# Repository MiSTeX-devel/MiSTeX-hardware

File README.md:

# MiSTeX-hardware

## Current
### MiSTeX baseboard for QMTech form factor FPGA boards
The 
baseboard is the current recommended platform. It can be used with Raspberry Pi Zero
form factor SBCs and QMTech form factor core boards.
Status: The `rev2` revision has been manufactured and tested working.

### Using the Raspberry Pi Zero with MiSTeX, with a generic FPGA board
To connect the Raspberry Pi Zero to the FPGA board of your choice,
the pin mappings can be found in two places:
1. On the FPGA board side the pin mappings are defined in the board support file in MiSTeX-boards:
   
2. On the Raspberry Pi Zero side, the pin mappings of the GPIO control signals are defined in Main_MiSTeX in fpga_io.cpp:

   And the SPI bus is the SPI0 on the Raspberry Pi header:

## Obsolete
### MiSTeX Pmod
Status: Manufactured, waiting for arrival. Obsolete, Sipeed Lich

### MiSTeX cape for the Terasic DECA board
Status: Manufactured and tested working.

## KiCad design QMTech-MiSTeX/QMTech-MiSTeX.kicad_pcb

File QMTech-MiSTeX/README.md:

# **MiSTeX Board**

### Connectors and main headers

- Headers for QMTech 128 pins FPGA format (2x 2x32)
- MiSTer SDRAM module header (Terasic 2x20)
- RPi header (Orange Pi 2W) (2x20)
- SNAC user port for gamepads / mt32pi (USB3)
- VGA video out (DB15)
- HDMI video out
- Analog audio out (delta sigma) (jack 3.5) 
- SPDID audio out (Toslink)
- Secondary uSD Card
- PMOD J11 header (GPIO / I2S / Delta-sigma)
- USB C for RP2040 programming
- USB C power supply

### Power Supply

It is recommended to use the USB power port since it uses a voltage filter. This port supply power to FPGA and Orange Pi as well.

The Jumper on the power port is for an external power switch mounted in a case for example. 

<u>J18 needs to be shorted with a jumper if no switch is placed</u>.

You can of course also power the board from the core board barrel jack.

### FPGA programming

Connect an USB-C from RP2040 port to the USB HUB you are using

Connect Dupont wires from FPGA JTAG to JTAG header on MiSTeX board

### Switches / Jumpers / small headers / Leds

J9 RC2040 Boot jumper. Short to reprogram RC2040 firmware

J10 SCART VGA pin 9 jumper. Short to use a VGA to SCART cable

J18 Power switch (or either place a jumper if no switch is added)

IO6 Jumper - By default shorted 2-3 for most gamepads. Some accessories require additional 3V3 power supply, in that case put jumper in position 1-2 next to +3V3 text.

SW1 Button User (RPi/Orange Pi)

SW2 Button OSD  (RPi/Orange Pi)

SW3 Button Reset  (RPi/Orange Pi)

SW4 Button Menu  (RPi/Orange Pi)

The side switches SW5, SW6 are currently unused and have been erroneously momentary in rev1, but should actually be latching which has been fixed in rev2

- SW5 (FPGA) will be used to switch the Pmod signals from I2S to general purpose use

- SW6 (RPi/Orange Pi)  is intended to switch the SNAC port from SNAC to mt32pi mode

The DIP switches are currently unused too  (RPi/Orange Pi).

User / HDD / Power Leds

DBG J7 Debug UART (RC2040)

SWD J12 Header (RC2040)

JTAG J6 Header   (RC2040)

ADC J14 Header (3 ADC + 1 GPIO)  (RC2040)

### SD image (placed at Orange Pi SD slot)

```sh
$ wget -c http://www.hans-baier.de/static/mistex-orangepizero2w.img.xz
$ md5sum mistex-orangepizero2w.img.xz
30ea6324ea5340d76d8ffbd25d986887  mistex-orangepizero2w.img.xz
```

The boot image needs the menu core at /media/fat/menu.bit
or menu.rbf for Altera boards
The sdcard image above is preconfigured for the Artix 100t QmTech with pre built cores
But A200T and K325T cores are included too
You only need to copy the right one to menu.bit

### RP2040 firmware

You need to bridge the boot jumper J9 and plug the RC2040 USB port into a PC to flash this firmware: https://github.com/MiSTeX-devel/pico-dirtyJtag/releases/tag/v0.0.1
The core FPGA board needs to be present there because it powers the 2040 except you power the 3.3v rails from another source.

Connect power supply either to FPGA barrel or USB-C power port.

Copy the uf2 file into the mass storage device that appears on PC. When the file disappears it means it is flashing the firmware. Wait a bit and disconnect USB-C and remove jumper.

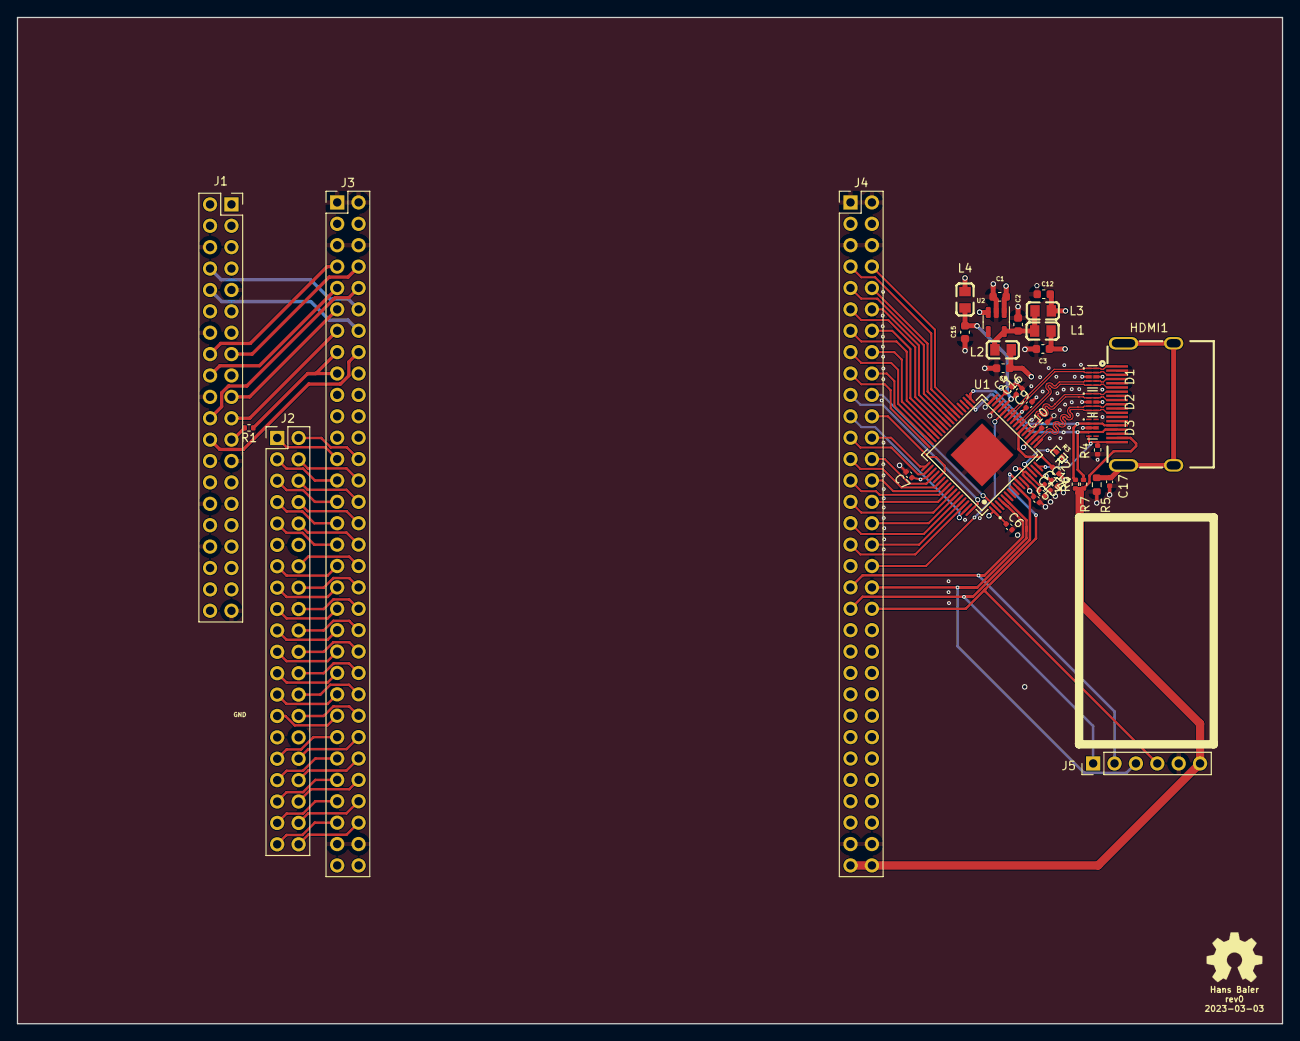
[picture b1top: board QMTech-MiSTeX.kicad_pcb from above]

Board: 4 copper layers, 150.2 x 119.5 mm, 40 parts (0 on the bottom side), 104 nets.

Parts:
C1: 1u; C_0603_1608Metric
C2, C3, C8, C12, C15: 10u; C_0603_1608Metric
C4, C5, C6, C7, C9, C10, C11, C13, C14, C16, C17: 100nF; C_0402_1005Metric
D1, D2, D3: TPD4E05U06DQAR_C2972498; DFN2510-10_L2.5-W1.0-P0.50-BL
HDMI1: HDMI-001S; HDMI-SMD_HDMI-001S
J1: RPi_GPIO; PinSocket_2x20_P2.54mm_Vertical
J2: MiSTer SDRAM Module; PinHeader_2x20_P2.54mm_Vertical
J3, J4: Conn_02x32_Odd_Even; PinHeader_2x32_P2.54mm_Vertical
J5: Conn_01x06_Male; PinHeader_1x06_P2.54mm_Vertical
L1, L2, L3, L4: 10uH; L0805
N1: OHWLOGO; OSHW-Symbol_6.7x6mm_SilkScreen
R1: 51R; R_0402_1005Metric
R2, R6, R7: 2k; R_0402_1005Metric
R3: 887R; R0402
R4: 10k; R_0402_1005Metric
R5: 1M; R_0603_1608Metric
U1: ADV7513BSWZ; LQFP-64_L10.0-W10.0-P0.50-LS12.0-BL-EP5.3
U2: TPS76318; SOT-23-5

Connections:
+1V8: C2.1, L1.1, L2.1, L3.1, U2.5 (VOUT)
+3V3: C1.1, J2.29, J3.3, J3.4, J4.3, J4.4, L4.1, U2.1 (VIN), U2.3 (EN)
+5V: HDMI1.18 (+5VPower), J1.2 (5V), J1.4 (5V), J2.11, J3.63, J3.64, J4.63, J4.64, J5.6, R6.1, R7.2
/1V8_AVDD: C8.1, C9.1, C10.1, C11.1, L2.2, U1.15 (AVDD), U1.19 (AVDD), U1.25 (AVDD)
/1V8_DVDD: C3.1, C4.1, C5.1, C6.1, C7.1, L1.2, U1.1 (DVDD), U1.11 (DVDD), U1.31 (DVDD), U1.51 (DVDD)
/1V8_PVDD: C12.1, C13.1, C14.1, L3.2, U1.12 (PVDD), U1.13 (BGVDD)
/3V3_DVDD: C15.1, C16.1, L4.2, U1.29 (DVDD_3V)
/DDC_SCL: D3.2 (D1-), D3.9 (NC), HDMI1.15 (SCL), R6.2, U1.33 (DDCSCL)
/DDC_SDA: D3.4 (D2+), D3.7 (NC), HDMI1.16 (SDA), R7.1, U1.34 (DDCSDA)
/FPGA_EN: J1.16 (GPIO23), J3.7
/FPGA_RESET: J1.15 (GPIO22), J3.8
/HDMI_CLK+: D2.4 (D2+), D2.7 (NC), HDMI1.10 (TMDSClock+), U1.18 (TXC+)
/HDMI_CLK-: D2.5 (D2-), D2.6 (NC), HDMI1.12 (TMDSClock-), U1.17 (TXC–)
/HDMI_HPD: D3.5 (D2-), HDMI1.19 (HotPlugDetect), R4.1, U1.16 (HPD)
/HDMI_TX0+: D2.1 (D1+), D2.10 (NC), HDMI1.7 (TMDSData0+), U1.21 (TX0+)
/HDMI_TX0-: D2.2 (D1-), D2.9 (NC), HDMI1.9 (TMDSData0-), U1.20 (TX0–)
/HDMI_TX1+: D1.4 (D2+), D1.7 (NC), HDMI1.4 (TMDSData1+), U1.24 (TX1+)
/HDMI_TX1-: D1.5 (D2-), D1.6 (NC), HDMI1.6 (TMDSData1-), U1.23 (TX1–)
/HDMI_TX2+: D1.1 (D1+), D1.10 (NC), HDMI1.1 (TMDSData2+), U1.27 (TX2+)
/HDMI_TX2-: D1.2 (D1-), D1.9 (NC), HDMI1.3 (TMDSData2-), U1.26 (TX2–)
/I2C_SCL: J1.5 (GPIO03_SCL1_I2C), U1.35 (SCL)
/I2C_SDA: J1.3 (GPIO02_SDA1_I2C), U1.36 (SDA)
/I2S_DAT: J4.38, J5.3, U1.5 (I2S0)
/I2S_LRCLK: J4.40, J5.4, U1.10 (LRCLK)
/I2S_MCLK: J4.37, J5.2, U1.4 (MCLK)
/I2S_SCLK: J4.39, J5.1, U1.9 (SCLK)
/IO_EN: J1.22 (GPIO25), J3.10
/OSD_EN: J1.18 (GPIO24), J3.9
/RAM_A0: J2.37, J3.57
/RAM_A1: J2.38, J3.58
/RAM_A2: J2.39, J3.59
/RAM_A3: J2.40, J3.60
/RAM_A4: J2.28, J3.50
/RAM_A5: J2.25, J3.47
/RAM_A6: J2.26, J3.48
/RAM_A7: J2.23, J3.45
/RAM_A8: J2.24, J3.46
/RAM_A9: J2.21, J3.43
/RAM_A10: J2.36, J3.56
/RAM_A11: J2.22, J3.44
/RAM_A12: J2.19, J3.41
/RAM_BA0: J2.34, J3.54
/RAM_BA1: J2.35, J3.55
/RAM_CAS: J2.31, J3.51
/RAM_CLK: J2.20, J3.42
/RAM_CS: J2.33, J3.53
/RAM_DQ0: J2.1, J3.25
/RAM_DQ1: J2.2, J3.26
/RAM_DQ2: J2.3, J3.27
/RAM_DQ3: J2.4, J3.28
/RAM_DQ4: J2.5, J3.29
/RAM_DQ5: J2.6, J3.30
/RAM_DQ6: J2.7, J3.31
/RAM_DQ7: J2.8, J3.32
/RAM_DQ8: J2.18, J3.40
/RAM_DQ9: J2.17, J3.39
/RAM_DQ10: J2.16, J3.38
/RAM_DQ11: J2.15, J3.37
/RAM_DQ12: J2.14, J3.36
/RAM_DQ13: J2.13, J3.35
/RAM_DQ14: J2.10, J3.34
/RAM_DQ15: J2.9, J3.33
/RAM_RAS: J2.32, J3.52
/RAM_WE: J2.27, J3.49
/RGB_CLK: J4.22, U1.53 (CLK)
/RGB_D0: J4.33, U1.62 (D0)
/RGB_D1: J4.34, U1.61 (D1)
/RGB_D2: J4.31, U1.60 (D2)
/RGB_D3: J4.32, U1.59 (D3)
/RGB_D4: J4.29, U1.58 (D4)
/RGB_D5: J4.30, U1.57 (D5)
/RGB_D6: J4.27, U1.56 (D6)
/RGB_D7: J4.28, U1.55 (D7)
/RGB_D8: J4.25, U1.54 (D8)
/RGB_D9: J4.26, U1.52 (D9)
/RGB_D10: J4.23, U1.50 (D10)
/RGB_D11: J4.24, U1.49 (D11)
/RGB_D12: J4.17, U1.48 (D12)
/RGB_D13: J4.18, U1.47 (D13)
/RGB_D14: J4.15, U1.46 (D14)
/RGB_D15: J4.16, U1.45 (D15)
/RGB_D16: J4.13, U1.44 (D16)
/RGB_D17: J4.14, U1.43 (D17)
/RGB_D18: J4.11, U1.42 (D18)
/RGB_D19: J4.12, U1.41 (D19)
/RGB_D20: J4.9, U1.40 (D20)
/RGB_D21: J4.10, U1.39 (D21)
/RGB_D22: J4.7, U1.38 (D22)
/RGB_D23: J4.8, U1.37 (D23)
/RGB_DE: J4.21, U1.63 (DE)
/RGB_HSYNC: J4.19, U1.64 (HSYNC)
/RGB_INT: J4.36, U1.28 (INT)
/RGB_VSYNC: J4.20, U1.2 (VSYNC)
/SPI_CLK: J3.15, J3.17, R1.1
/SPI_CS: J1.24 (GPIO08_SPI_CE0_N), J3.16
/SPI_MISO: J1.21 (GPIO09_SPI_MISO), J3.13
/SPI_MOSI: J1.19 (GPIO10_SPI_MOSI), J3.11
/UART_RX: J1.10 (GPIO15_RXD0), J3.14
/UART_TX: J1.8 (GPIO14_TXD0), J3.12
GND: C1.2, C2.2, C3.2, C4.2, C5.2, C6.2, C7.2, C8.2, C9.2, C10.2, C11.2, C12.2, C13.2, C14.2, C15.2, C16.2, C17.2, D1.3 (GND), D1.8 (GND), D2.3 (GND), D2.8 (GND), D3.3 (GND), D3.8 (GND), HDMI1.2 (TMDSData2Shield), HDMI1.5 (TMDSData1Shield), HDMI1.8 (TMDSData0Shield), HDMI1.11 (TMDSClockShield), HDMI1.17 (DDC/CECGround), J1.6 (GND), J1.9 (GND), J1.14 (GND), J1.20 (GND), J1.25 (GND), J1.30 (GND), J1.34 (GND), J1.39 (GND), J2.12, J2.30, J3.1, J3.2, J3.5, J3.6, J3.61, J3.62, J4.1, J4.2, J4.5, J4.6, J4.61, J4.62, J5.5, R2.2, R3.1, R4.2, R5.2, U1.30 (CEC), U1.32 (CEC_CLK), U1.65 (EP), U2.2 (GND)
unnamed: C17.1, HDMI1.20 (GND), HDMI1.21 (GND), HDMI1.22 (GND), HDMI1.23 (GND), R5.1
unnamed: J1.23 (GPIO11_SPI_CLK), R1.2
unnamed: R2.1, U1.22 (PD)
unnamed: R3.2, U1.14 (R_EXT)

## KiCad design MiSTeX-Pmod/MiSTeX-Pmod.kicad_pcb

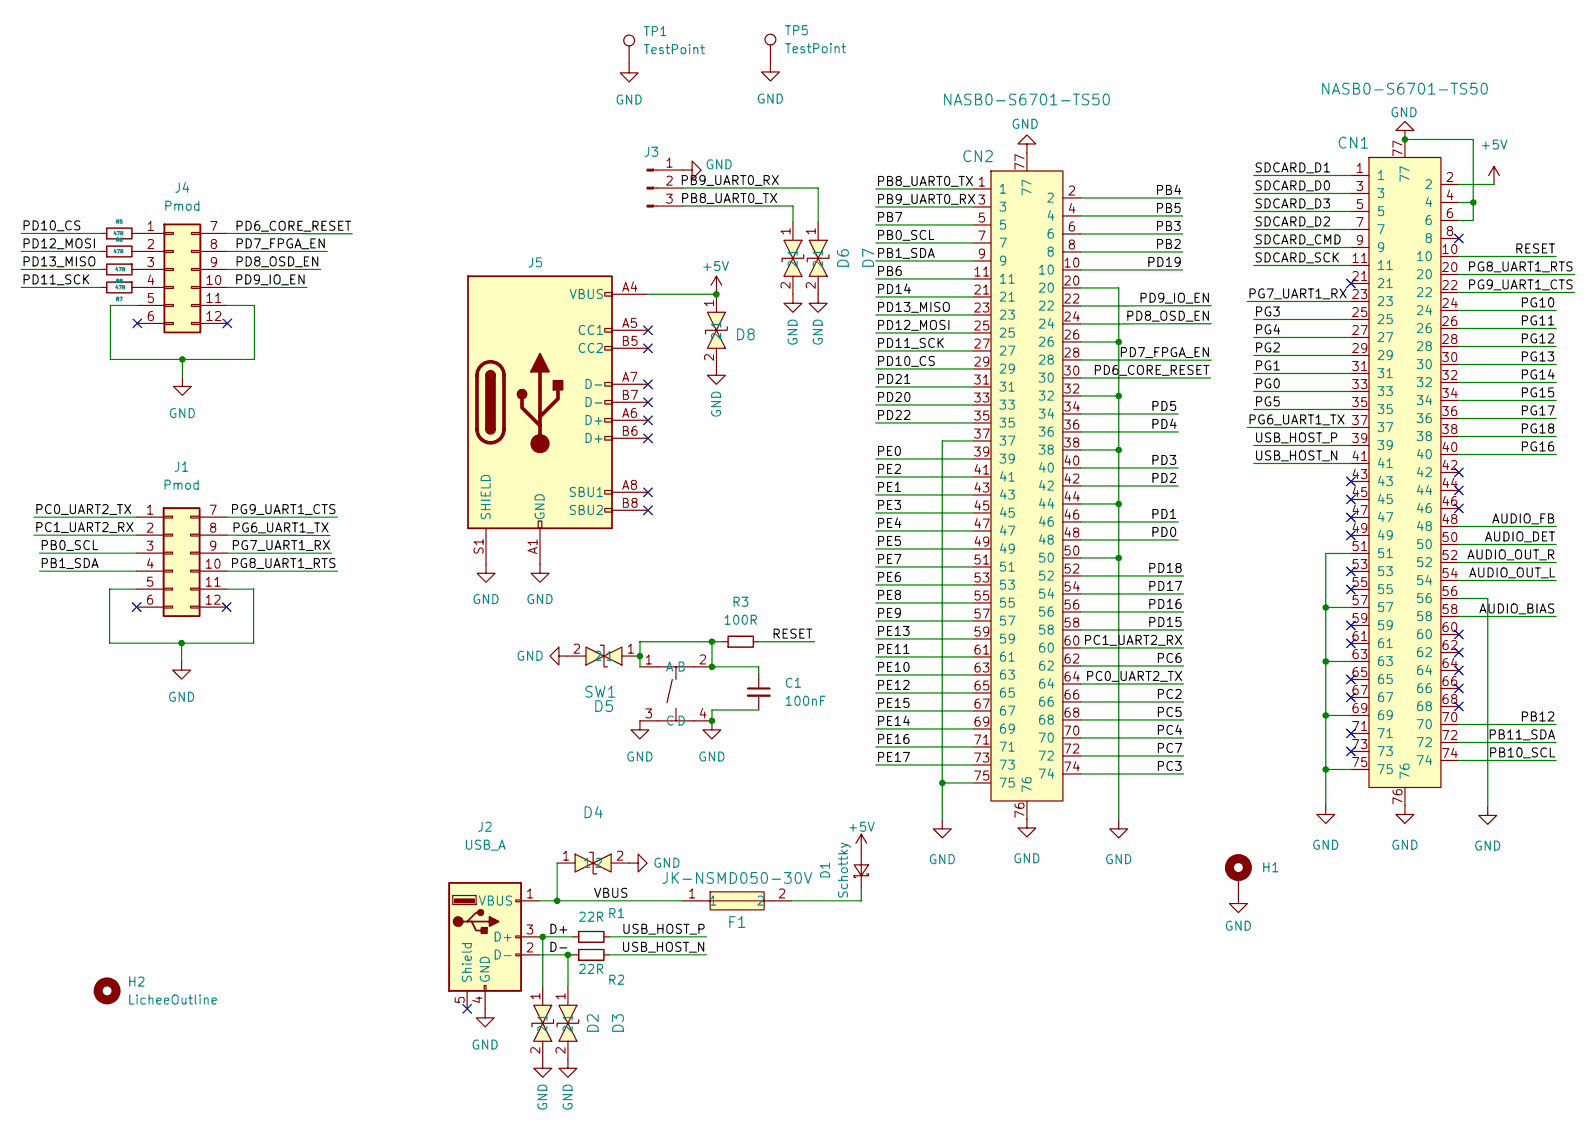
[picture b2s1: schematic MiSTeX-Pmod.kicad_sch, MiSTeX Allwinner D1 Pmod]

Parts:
C1: 100nF; C_0402_1005Metric; LCSC C1525
CN1, CN2: NASB0-S6701-TS50; CONN-SMD_67P-P0.50-V_NASB0-S6701-TS50; LCSC Part C367024
D1: Schottky; D_SMA; LCSC C22452
D2, D3, D4, D5, D6, D7, D8: LXES15AAA1-133; D0402-BI; LCSC Part C191267
F1: JK-NSMD050-30V; F1206; LCSC Part C720075
H1: MountingHole_Pad; MountingHole_2.2mm_M2_ISO7380_Pad_TopBottom
H2: LicheeOutline
J1, J4: Pmod; Pmod 2x6
J2: USB_A; USB-A-SMD_GT-USB-2004-CWG1A; LCSC C5117890
J3: Conn_01x03_Male; PinHeader_1x03_P2.54mm_Vertical
J5: Connector_USB_C_Receptacle_USB2.0; USB-C_SMD-TYPE-C-31-M-12; LCSC C165948
R1, R2: 22R; R_0402_1005Metric; LCSC C25092
R3: 100R; R_0402_1005Metric; LCSC C25076
R5, R6, R7, R8: 47R; R_0402_1005Metric; LCSC C25118
SW1: TS-1187A-B-A-B; SW-SMD_4P-L5.1-W5.1-P3.70-LS6.5-TL-2; LCSC Part C318884
TP1: TestPoint; TestPoint_Pad_D2.0mm
TP5: TestPoint; TestPoint_Pad_D1.0mm

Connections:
+5V: CN1.2, D1.2 (A), D8.1, J5.A4 (VBUS), J5.A9 (VBUS), J5.B4 (VBUS), J5.B9 (VBUS)
/AUDIO_BIAS: CN1.58
/AUDIO_DET: CN1.50
/AUDIO_FB: CN1.48
/AUDIO_OUT_L: CN1.54
/AUDIO_OUT_R: CN1.52
/D+: D2.1, J2.3 (D+), R1.1
/D-: D3.1, J2.2 (D-), R2.1
/PB0_SCL: CN2.7, J1.3
/PB1_SDA: CN2.9, J1.4
/PB2: CN2.8
/PB3: CN2.6
/PB4: CN2.2
/PB5: CN2.4
/PB6: CN2.11
/PB7: CN2.5
/PB8_UART0_TX: CN2.1, D6.1, J3.3
/PB9_UART0_RX: CN2.3, D7.1, J3.2
/PB10_SCL: CN1.74
/PB11_SDA: CN1.72
/PB12: CN1.70
/PC0_UART2_TX: CN2.64, J1.1
/PC1_UART2_RX: CN2.60, J1.2
/PC2: CN2.66
/PC3: CN2.74
/PC4: CN2.70
/PC5: CN2.68
/PC6: CN2.62
/PC7: CN2.72
/PD0: CN2.48
/PD1: CN2.46
/PD2: CN2.42
/PD3: CN2.40
/PD4: CN2.36
/PD5: CN2.34
/PD6_CORE_RESET: CN2.30, J4.7
/PD7_FPGA_EN: CN2.28, J4.8
/PD8_OSD_EN: CN2.24, J4.9
/PD9_IO_EN: CN2.22, J4.10
/PD10_CS: CN2.29, R5.1
/PD11_SCK: CN2.27, R7.2
/PD12_MOSI: CN2.25, R6.1
/PD13_MISO: CN2.23, R8.2
/PD14: CN2.21
/PD15: CN2.58
/PD16: CN2.56
/PD17: CN2.54
/PD18: CN2.52
/PD19: CN2.10
/PD20: CN2.33
/PD21: CN2.31
/PD22: CN2.35
/PE0: CN2.39
/PE1: CN2.43
/PE2: CN2.41
/PE3: CN2.45
/PE4: CN2.47
/PE5: CN2.49
/PE6: CN2.53
/PE7: CN2.51
/PE8: CN2.55
/PE9: CN2.57
/PE10: CN2.63
/PE11: CN2.61
/PE12: CN2.65
/PE13: CN2.59
/PE14: CN2.69
/PE15: CN2.67
/PE16: CN2.71
/PE17: CN2.73
/PG0: CN1.33
/PG1: CN1.31
/PG2: CN1.29
/PG3: CN1.25
/PG4: CN1.27
/PG5: CN1.35
/PG6_UART1_TX: CN1.37, J1.8
/PG7_UART1_RX: CN1.23, J1.9
/PG8_UART1_RTS: CN1.20, J1.10
/PG9_UART1_CTS: CN1.22, J1.7
/PG10: CN1.24
/PG11: CN1.26
/PG12: CN1.28
/PG13: CN1.30
/PG14: CN1.32
/PG15: CN1.34
/PG16: CN1.40
/PG17: CN1.36
/PG18: CN1.38
/RESET: CN1.10, R3.2
/SDCARD_CMD: CN1.9
/SDCARD_D0: CN1.3
/SDCARD_D1: CN1.1
/SDCARD_D2: CN1.7
/SDCARD_D3: CN1.5
/SDCARD_SCK: CN1.11
/USB_HOST_N: CN1.41, R2.2
/USB_HOST_P: CN1.39, R1.2
/VBUS: D4.1, F1.1, J2.1 (VBUS)
GND: C1.2, CN1.4, CN1.6, CN1.51, CN1.56, CN1.57, CN1.63, CN1.69, CN1.75, CN1.76, CN1.77, CN2.20, CN2.26, CN2.32, CN2.37, CN2.38, CN2.44, CN2.50, CN2.75, CN2.76, CN2.77, D2.2, D3.2, D4.2, D5.2, D6.2, D7.2, D8.2, H1.1, J1.5, J1.11, J2.4 (GND), J3.1, J4.5, J4.11, J5.A1 (GND), J5.A12 (GND), J5.B1 (GND), J5.B12 (GND), J5.S1 (SHIELD), SW1.3 (C), SW1.4 (D), TP1.1, TP5.1
unnamed: C1.1, D5.1, R3.1, SW1.1 (A), SW1.2 (B)
unnamed: D1.1 (K), F1.2
unnamed: J4.1, R5.2
unnamed: J4.2, R6.2
unnamed: J4.3, R8.1
unnamed: J4.4, R7.1

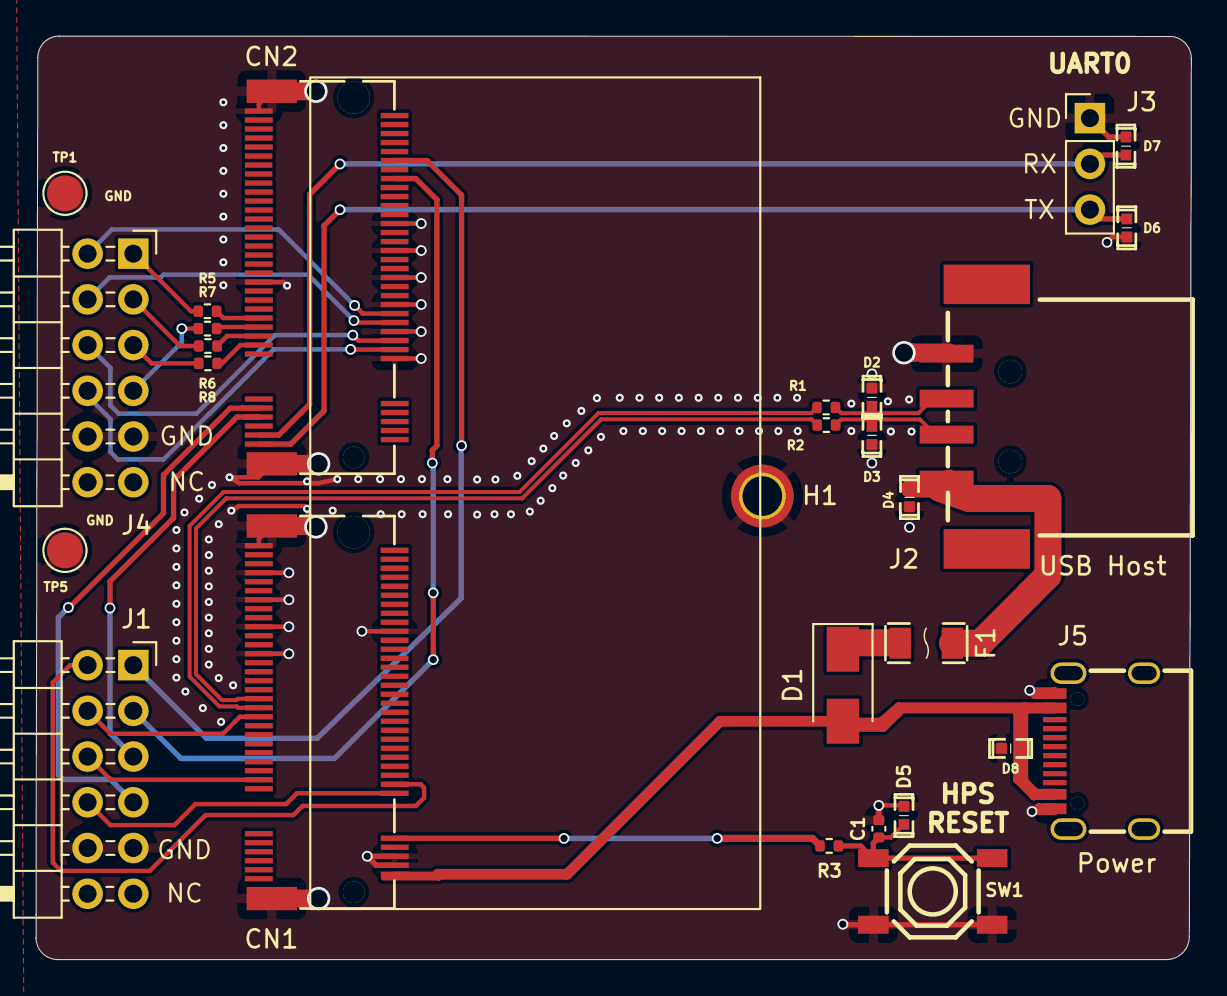
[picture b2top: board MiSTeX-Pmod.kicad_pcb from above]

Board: 4 copper layers, 64.2 x 51.3 mm, 30 parts (0 on the bottom side), 32 nets.

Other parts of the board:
N1: OHWLOGO; OSHW-Symbol_6.7x6mm_SilkScreen

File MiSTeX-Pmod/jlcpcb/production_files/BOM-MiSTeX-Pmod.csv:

Comment,Designator,Footprint,LCSC
100nF,C1,C_0402_1005Metric,C1525
Connector_USB_C_Receptacle_USB2.0,J5,USB-C_SMD-TYPE-C-31-M-12,C165948
LXES15AAA1-133,"D2,D3,D4,D5,D6,D7,D8",D0402-BI,C191267
Schottky,D1,D_SMA,C22452
100R,R3,R_0402_1005Metric,C25076
22R,"R1,R2",R_0402_1005Metric,C25092
47R,"R5,R6,R7,R8",R_0402_1005Metric,C25118
TS-1187A-B-A-B,SW1,SW-SMD_4P-L5.1-W5.1-P3.70-LS6.5-TL-2,C318884
NASB0-S6701-TS50,"CN1,CN2",CONN-SMD_67P-P0.50-V_NASB0-S6701-TS50,C367024
USB_A,J2,USB-A-SMD_GT-USB-2004-CWG1A,C5117890
JK-NSMD050-30V,F1,F1206,C720075
TestPoint,TP1,TestPoint_Pad_D2.0mm,
Pmod,J1,Pmod 2x6,
TestPoint,TP5,TestPoint_Pad_D2.0mm,
Conn_01x03_Male,J3,PinHeader_1x03_P2.54mm_Vertical,
Pmod,J4,Pmod 2x6,
MountingHole_Pad,H1,MountingHole_2.2mm_M2_ISO7380_Pad_TopBottom,
Sipeed Lichee,H2,Sipeed Lichee,

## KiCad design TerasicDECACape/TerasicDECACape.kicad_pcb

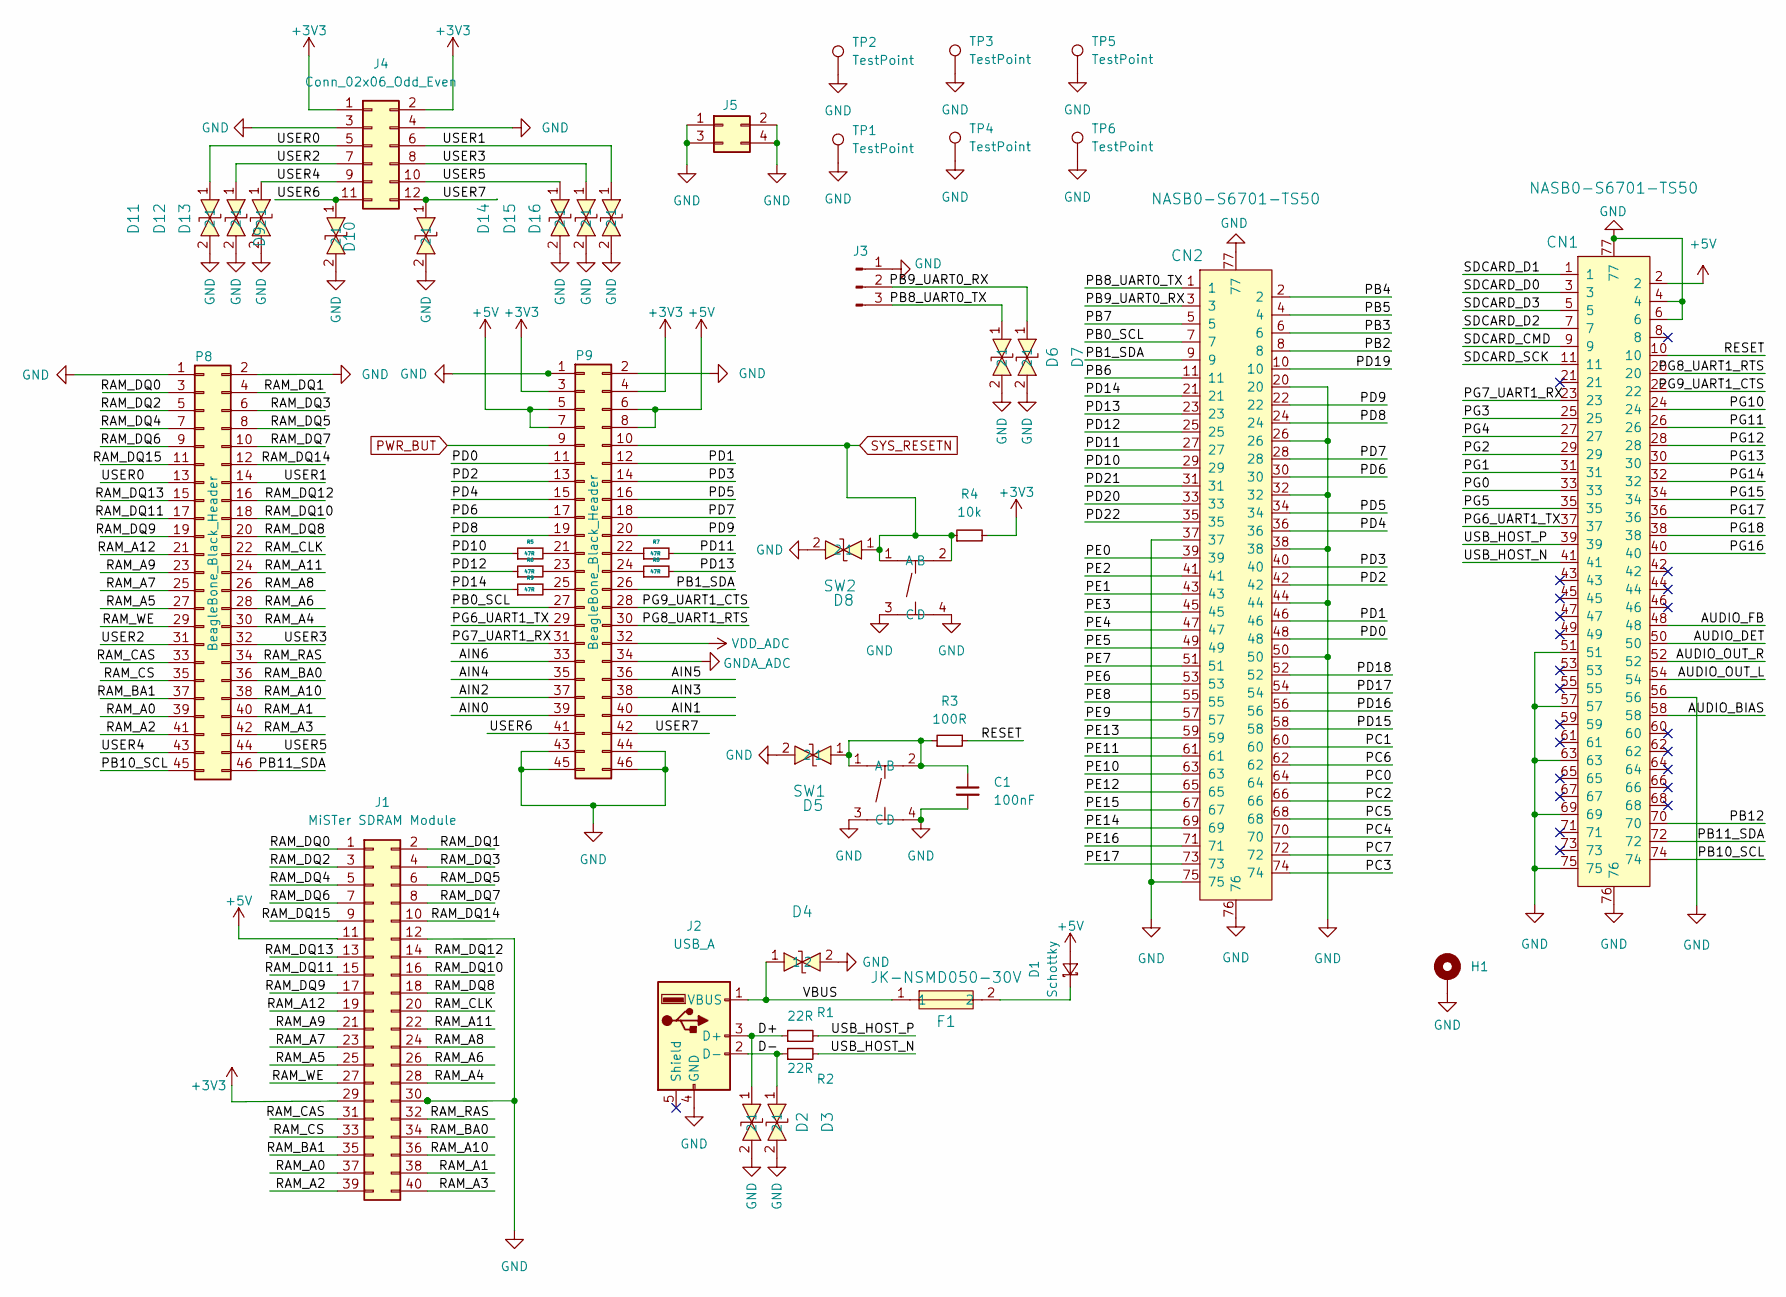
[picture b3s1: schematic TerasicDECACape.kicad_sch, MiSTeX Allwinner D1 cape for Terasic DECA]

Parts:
C1: 100nF; C_0402_1005Metric; LCSC C1525
CN1, CN2: NASB0-S6701-TS50; CONN-SMD_67P-P0.50-V_NASB0-S6701-TS50; LCSC Part C367024
D1: Schottky; D_SMA; LCSC C22452
D2, D3, D4, D5, D6, D7, D8, D9, D10, D11, D12, D13, D14, D15, D16: LXES15AAA1-133; D0402-BI; LCSC Part C191267
F1: JK-NSMD050-30V; F1206; LCSC Part C720075
H1: MountingHole_Pad; MountingHole_2.2mm_M2_ISO7380_Pad_TopBottom
J1: MiSTer SDRAM Module; PinHeader_2x20_P2.54mm_Vertical
J2: USB_A; USB-A-SMD_USB-302S; LCSC C112455
J3: Conn_01x03_Male; PinHeader_1x03_P2.54mm_Vertical
J4: Conn_02x06_Odd_Even; PinSocket_2x06_P2.54mm_Vertical
J5: Conn_02x02_Odd_Even; PinHeader_2x02_P2.54mm_Vertical
P8, P9: BeagleBone_Black_Header; Socket_BeagleBone_Black
R1, R2: 22R; R_0402_1005Metric; LCSC C25092
R3: 100R; R_0402_1005Metric; LCSC C25076
R4: 10k; R_0402_1005Metric; LCSC C25744
R5, R6, R7, R8, R9: 47R; R_0402_1005Metric; LCSC C25118
SW1, SW2: TS-1187A-B-A-B; SW-SMD_4P-L5.1-W5.1-P3.70-LS6.5-TL-2; LCSC Part C318884
TP1, TP4: TestPoint; TestPoint_Pad_D2.0mm
TP2, TP3, TP5, TP6: TestPoint; TestPoint_Pad_D1.0mm

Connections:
+3V3: J1.29, J4.1, J4.2, P9.3, P9.4, R4.2
+5V: CN1.2, D1.2 (A), J1.11, P9.5, P9.6, P9.7, P9.8
/AIN0: P9.39
/AIN1: P9.40
/AIN2: P9.37
/AIN3: P9.38
/AIN4: P9.35
/AIN5: P9.36
/AIN6: P9.33
/AUDIO_BIAS: CN1.58
/AUDIO_DET: CN1.50
/AUDIO_FB: CN1.48
/AUDIO_OUT_L: CN1.54
/AUDIO_OUT_R: CN1.52
/D+: D2.1, J2.3 (D+), R1.1
/D-: D3.1, J2.2 (D-), R2.1
/PB0_SCL: CN2.7, P9.27
/PB1_SDA: CN2.9, P9.26
/PB2: CN2.8
/PB3: CN2.6
/PB4: CN2.2
/PB5: CN2.4
/PB6: CN2.11
/PB7: CN2.5
/PB8_UART0_TX: CN2.1, D6.1, J3.3
/PB9_UART0_RX: CN2.3, D7.1, J3.2
/PB10_SCL: CN1.74, P8.45
/PB11_SDA: CN1.72, P8.46
/PB12: CN1.70
/PC0: CN2.64
/PC1: CN2.60
/PC2: CN2.66
/PC3: CN2.74
/PC4: CN2.70
/PC5: CN2.68
/PC6: CN2.62
/PC7: CN2.72
/PD0: CN2.48, P9.11
/PD1: CN2.46, P9.12
/PD2: CN2.42, P9.13
/PD3: CN2.40, P9.14
/PD4: CN2.36, P9.15
/PD5: CN2.34, P9.16
/PD6: CN2.30, P9.17
/PD7: CN2.28, P9.18
/PD8: CN2.24, P9.19
/PD9: CN2.22, P9.20
/PD10: CN2.29, R5.1
/PD11: CN2.27, R7.2
/PD12: CN2.25, R6.1
/PD13: CN2.23, R8.2
/PD14: CN2.21, R9.1
/PD15: CN2.58
/PD16: CN2.56
/PD17: CN2.54
/PD18: CN2.52
/PD19: CN2.10
/PD20: CN2.33
/PD21: CN2.31
/PD22: CN2.35
/PE0: CN2.39
/PE1: CN2.43
/PE2: CN2.41
/PE3: CN2.45
/PE4: CN2.47
/PE5: CN2.49
/PE6: CN2.53
/PE7: CN2.51
/PE8: CN2.55
/PE9: CN2.57
/PE10: CN2.63
/PE11: CN2.61
/PE12: CN2.65
/PE13: CN2.59
/PE14: CN2.69
/PE15: CN2.67
/PE16: CN2.71
/PE17: CN2.73
/PG0: CN1.33
/PG1: CN1.31
/PG2: CN1.29
/PG3: CN1.25
/PG4: CN1.27
/PG5: CN1.35
/PG6_UART1_TX: CN1.37, P9.29
/PG7_UART1_RX: CN1.23, P9.31
/PG8_UART1_RTS: CN1.20, P9.30
/PG9_UART1_CTS: CN1.22, P9.28
/PG10: CN1.24
/PG11: CN1.26
/PG12: CN1.28
/PG13: CN1.30
/PG14: CN1.32
/PG15: CN1.34
/PG16: CN1.40
/PG17: CN1.36
/PG18: CN1.38
/RAM_A0: J1.37, P8.39
/RAM_A1: J1.38, P8.40
/RAM_A2: J1.39, P8.41
/RAM_A3: J1.40, P8.42
/RAM_A4: J1.28, P8.30
/RAM_A5: J1.25, P8.27
/RAM_A6: J1.26, P8.28
/RAM_A7: J1.23, P8.25
/RAM_A8: J1.24, P8.26
/RAM_A9: J1.21, P8.23
/RAM_A10: J1.36, P8.38
/RAM_A11: J1.22, P8.24
/RAM_A12: J1.19, P8.21
/RAM_BA0: J1.34, P8.36
/RAM_BA1: J1.35, P8.37
/RAM_CAS: J1.31, P8.33
/RAM_CLK: J1.20, P8.22
/RAM_CS: J1.33, P8.35
/RAM_DQ0: J1.1, P8.3
/RAM_DQ1: J1.2, P8.4
/RAM_DQ2: J1.3, P8.5
/RAM_DQ3: J1.4, P8.6
/RAM_DQ4: J1.5, P8.7
/RAM_DQ5: J1.6, P8.8
/RAM_DQ6: J1.7, P8.9
/RAM_DQ7: J1.8, P8.10
/RAM_DQ8: J1.18, P8.20
/RAM_DQ9: J1.17, P8.19
/RAM_DQ10: J1.16, P8.18
/RAM_DQ11: J1.15, P8.17
/RAM_DQ12: J1.14, P8.16
/RAM_DQ13: J1.13, P8.15
/RAM_DQ14: J1.10, P8.12
/RAM_DQ15: J1.9, P8.11
/RAM_RAS: J1.32, P8.34
/RAM_WE: J1.27, P8.29
/RESET: CN1.10, R3.2
/SDCARD_CMD: CN1.9
/SDCARD_D0: CN1.3
/SDCARD_D1: CN1.1
/SDCARD_D2: CN1.7
/SDCARD_D3: CN1.5
/SDCARD_SCK: CN1.11
/USB_HOST_N: CN1.41, R2.2
/USB_HOST_P: CN1.39, R1.2
/USER0: D11.1, J4.5, P8.13
/USER1: D16.1, J4.6, P8.14
/USER2: D12.1, J4.7, P8.31
/USER3: D15.1, J4.8, P8.32
/USER4: D13.1, J4.9, P8.43
/USER5: D14.1, J4.10, P8.44
/USER6: D9.1, J4.11, P9.41
/USER7: D10.1, J4.12, P9.42
/VBUS: D4.1, F1.1, J2.1 (VBUS)
GND: C1.2, CN1.4, CN1.6, CN1.51, CN1.56, CN1.57, CN1.63, CN1.69, CN1.75, CN1.76, CN1.77, CN2.20, CN2.26, CN2.32, CN2.37, CN2.38, CN2.44, CN2.50, CN2.75, CN2.76, CN2.77, D2.2, D3.2, D4.2, D5.2, D6.2, D7.2, D8.2, D9.2, D10.2, D11.2, D12.2, D13.2, D14.2, D15.2, D16.2, H1.1, J1.12, J1.30, J2.4 (GND), J3.1, J4.3, J4.4, J5.1, J5.2, J5.3, J5.4, P8.1, P8.2, P9.1, P9.2, P9.43, P9.44, P9.45, P9.46, SW1.3 (C), SW1.4 (D), SW2.3 (C), SW2.4 (D), TP1.1, TP2.1, TP3.1, TP4.1, TP5.1, TP6.1
GNDA_ADC: P9.34
unnamed: C1.1, D5.1, R3.1, SW1.1 (A), SW1.2 (B)
unnamed: D1.1 (K), F1.2
unnamed: P9.21, R5.2
unnamed: P9.22, R7.1
unnamed: P9.23, R6.2
unnamed: P9.24, R8.1
unnamed: P9.25, R9.2
PWR_BUT: P9.9
SYS_RESETN: D8.1, P9.10, R4.1, SW2.1 (A), SW2.2 (B)
VDD_ADC: P9.32

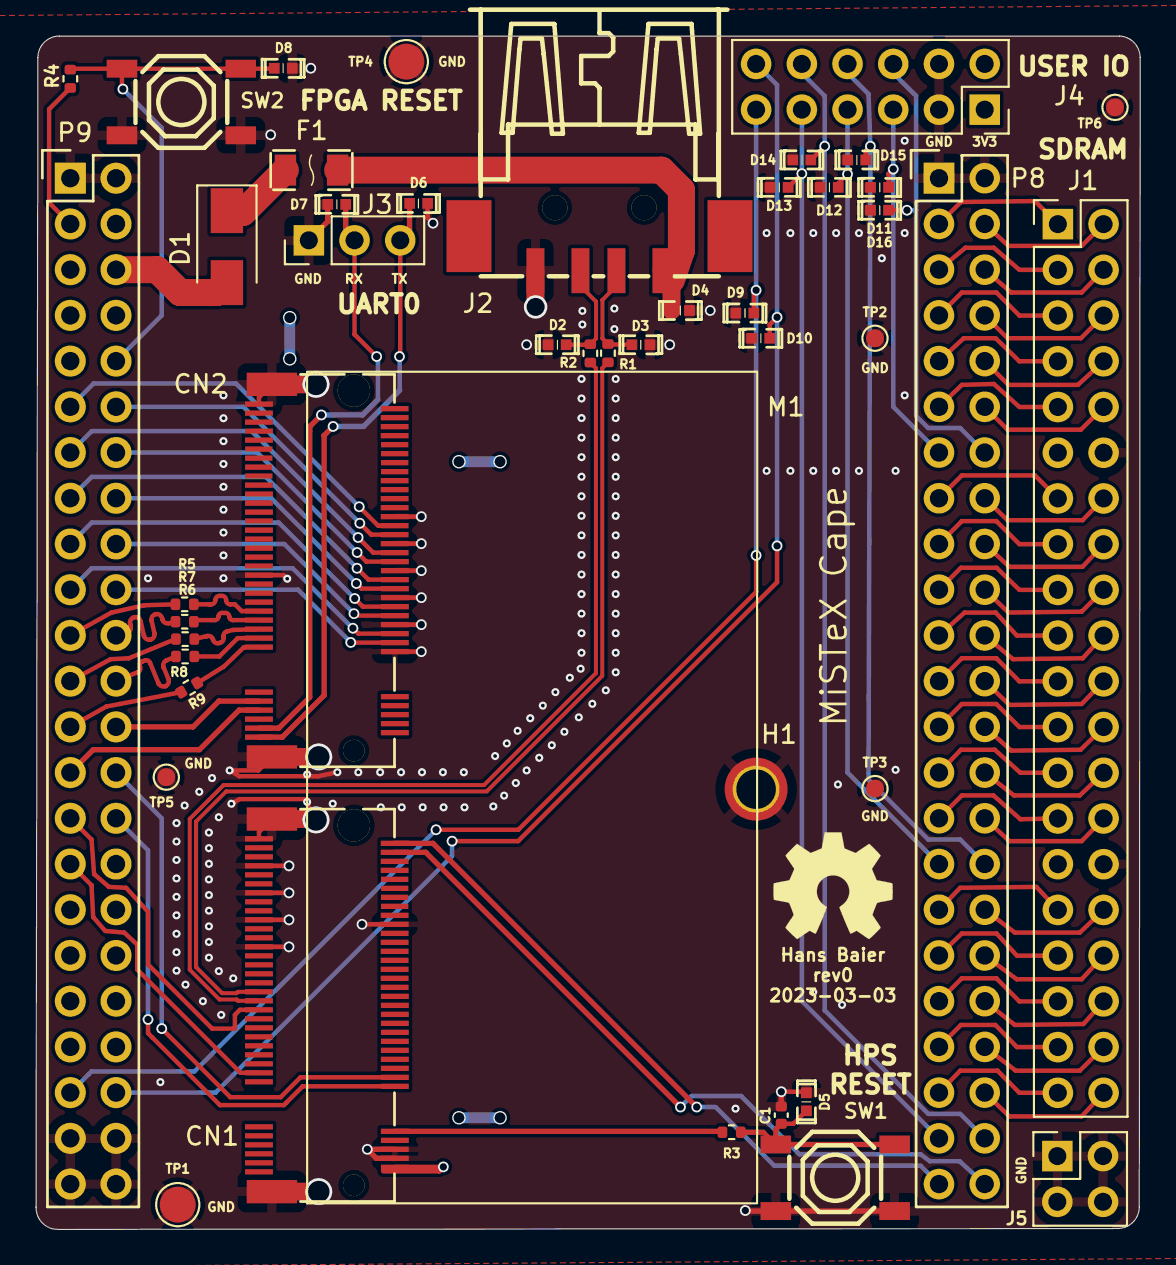
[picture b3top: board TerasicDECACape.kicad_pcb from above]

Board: 4 copper layers, 61.3 x 66.3 mm, 47 parts (0 on the bottom side), 86 nets.

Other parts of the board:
M1: Sipeed Lichee
N1: OHWLOGO; OSHW-Symbol_6.7x6mm_SilkScreen

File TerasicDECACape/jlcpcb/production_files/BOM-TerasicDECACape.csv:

Comment,Designator,Footprint,LCSC
USB_A,J2,USB-A-SMD_USB-302S,C112455
100nF,C1,C_0402_1005Metric,C1525
LXES15AAA1-133,"D10,D11,D12,D13,D14,D15,D16,D2,D3,D4,D5,D6,D7,D8,D9",D0402-BI,C191267
Schottky,D1,D_SMA,C22452
100R,R3,R_0402_1005Metric,C25076
22R,"R1,R2",R_0402_1005Metric,C25092
47R,"R5,R6,R7,R8,R9",R_0402_1005Metric,C25118
10k,R4,R_0402_1005Metric,C25744
TS-1187A-B-A-B,"SW1,SW2",SW-SMD_4P-L5.1-W5.1-P3.70-LS6.5-TL-2,C318884
NASB0-S6701-TS50,"CN1,CN2",CONN-SMD_67P-P0.50-V_NASB0-S6701-TS50,C367024
JK-NSMD050-30V,F1,F1206,C720075
BeagleBone_Black_Header,P8,Socket_BeagleBone_Black,
BeagleBone_Black_Header,P9,Socket_BeagleBone_Black,
MiSTer SDRAM Module,J1,PinHeader_2x20_P2.54mm_Vertical,
Conn_01x03_Male,J3,PinHeader_1x03_P2.54mm_Vertical,
Conn_02x06_Odd_Even,J4,PinSocket_2x06_P2.54mm_Vertical,
MountingHole_Pad,H1,MountingHole_2.2mm_M2_ISO7380_Pad_TopBottom,
Sipeed Lichee,M1,Sipeed Lichee,
TestPoint,TP1,TestPoint_Pad_D2.0mm,
TestPoint,TP6,TestPoint_Pad_D1.0mm,
TestPoint,TP4,TestPoint_Pad_D2.0mm,
TestPoint,TP2,TestPoint_Pad_D1.0mm,
TestPoint,TP5,TestPoint_Pad_D1.0mm,
Conn_02x02_Odd_Even,J5,PinHeader_2x02_P2.54mm_Vertical,
TestPoint,TP3,TestPoint_Pad_D1.0mm,

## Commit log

2023-03-01 first take on the board, needs review
2023-03-01 add mounting hole for module
2023-03-01 add user IO header, connect UART1 with flow control
2023-03-01 add title block data
2023-03-01 fix DRC issues
2023-03-01 add ESD to user header
2023-03-01 schematic and PCB cosmetics
2023-03-02 remove LEDs, because we have enough on the base board, add their pins to USER IO
2023-03-02 tidy, make it ready for production
2023-03-02 fix swapped SDRAM net names on both headers, fix impedance on USB diff pair, add SPI termination resistors
2023-03-02 silkscreen cosmetics
2023-03-02 add ground headers, ground test points and ground vias
2023-03-02 fix tracks running above plane split
2023-03-02 silk screen fix
2023-03-02 add JLCPCB production files
2023-03-02 Silkscreen: Add board name, credits and OSHW logo
2023-03-03 add JLCPCB assembly files
2023-04-14 first version of the Pmod
2023-04-14 change USB host connector, old one was out of stock
2023-04-14 add production files
2023-04-14 Create LICENSE
2023-04-18 update schematic title
2023-05-15 MiSTeX Pmod: fix USB emc protection diode stubs
2023-11-07 README.md: Add pinout for Raspberry Pi Zero
2024-01-19 First WIP version of QMTech-MiSTeX baseboard
2024-01-19 show the schematic borders and fix the design to fit
2024-01-19 put the MiSTeX mascot on the schematic pages
2024-01-19 move SNAC into its own sheet
2024-01-20 fix SNAC pinout to match with the mapping described in sys/mt32pi.v
2024-01-20 apply review notes from somhi, move audio into its own subsheet, add analog audio out
2024-01-20 add I2C to FPGA pins
2024-01-21 add UART connections
2024-01-22 QMTech-MiSTeX: make I2S audio to the DVI optional, use SPDIF by default
2024-01-23 finish routing/layouting, fix silk screen, add mounting holes
2024-01-23 remove no unused SNAC schematic (has been combined with UserInterface)
2024-01-23 fix DRC errors and some warnings too
2024-01-23 Add some datasheets/technical doc PDFs
2024-01-23 get rid of SNAC mode switch and add OSD button instead
2024-01-23 move RP2040 to the top of the PCB, because it was on the wrong side of the core board
2024-01-23 moved the pi reset button from under the pi to the rest of the buttons
2024-01-23 add ground via on SPI clock probe
2024-01-23 add silk screen labels for ufl probes
2024-01-23 swap locations of power port and micro sd
2024-01-23 fix power port label
2024-01-23 add a power switch and break out and break out 4 more GPIOs on RP2040
2024-01-23 add test points for VGA signals
2024-01-23 add GND label
2024-01-23 fix rp2040 usb running over a power plane split
2024-01-23 update drc exclusions
2024-01-24 tidy schematic and exclude pin headers from BoM
2024-02-05 add HDMI chip documentation
2024-02-05 QMTech-MiSTeX: OSHW logo on front mask, add instructions for installing SDRAM
2024-02-07 add Terasic DECA Cape fp-lib-table
2024-02-07 add backups to gitignore
2024-02-07 rename Datasheets to doc and add DE10 Nano step file
2024-02-07 QMTech-MiSTeX WIP
2024-02-08 power filtering, testpoints, bottom caps, more decoupling, teardrops
2024-02-08 remove power switch because of bad quality, add BOM/CPL
2024-02-08 MiSTeX-Pmod: add missing assembly files
2024-02-08 remove raw gerber files. we already have the .zip
2024-02-08 ignore gerber dir
2024-02-09 QMTech-MiSTeX: fix swapped DQ14/15 pins
2024-02-11 connect buttons to the HPS, not the FPGA, because the FPGA does not use them
2024-02-14 use stricter design rules and cleanup all DRC errors
2024-02-14 silkscreen, schematic titles
2024-02-15 connect two remaining pins to new 2 row Pmod, fix via, tidy test points
2024-02-15 don't include DNP parts in BOM
2024-02-15 add vias in testpoints to facilitate scope probes
2024-02-15 add front switch, reroute USB, test points
2024-02-16 Add VGA green probe, add DIP switches, add to silk screen, cosmetics
2024-02-16 add gnd via and remove orphaned silk screen text
2024-02-16 Add ESD protection to headphone jack and Pmod
2024-02-16 remove audio debug UART header, we already have it on the Pmod
2024-02-16 add ground vias
2024-02-17 add CC1 and CC2 resistors to power connector
2024-02-19 add pin headers for buttons, add LED to RP2040, break out ADCs
2024-02-19 Redesign FPGA core board headers to be assembled at the fab
2024-02-19 Use yellow LED for RP2040, because green is out of stock
2024-02-20 Add power switch header
2024-02-21 add ground pin near USB test points, add GND vias to rp2040 center pad
2024-02-22 Order for rev1 is out to the fab
2024-02-24 add headers for LEDs
2024-03-07 fix side switches, vias under uFL connectors, silk screen
2024-03-16 add QMTech-MiSTeX baseboard foto
2024-03-25 Complete HOW_TO_ORDER.md
2024-03-25 update to KiCAD 8 and regenerate production files, with latching switches
2024-03-25 fix SW5,SW6, make them latching
2024-03-25 fix silkscreen names, sizes and positions after update pcb mess
2024-03-25 kicad 8 fixes (3d model paths)
2024-03-25 add easyeda2kicad submodule
2024-03-26 add rp2040 vbus, bump rev date, add USB_BOOT connection to RPi
2024-03-27 PDF Schematic for easy reference
2024-03-30 Update README.md, new download URL
2024-04-02 add MiSTeX Kun big logo, swap ferrite bead with in-stock part
2024-04-02 update revision date
